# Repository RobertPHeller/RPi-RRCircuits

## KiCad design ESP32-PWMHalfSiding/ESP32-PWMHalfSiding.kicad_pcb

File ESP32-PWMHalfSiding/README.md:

# ESP32-PWMHalfSiding

This is a circuit board that supports an ESP32 Dev Kit board or TTGO-T1 board 
to manage one half (one end) of a siding.  This board can also be used to 
manage two bi-directional single track ABS blocks or one bi-directional dual 
track ABS block.  There are other trackwork cases this board can handle as 
well.  

The board contains these I/O sections:

- Two occupancy detectors.  These are optoisolator based, so they will 
  work for both DC and DCC systems.
- Two stall-motor with point sense.
- Sixteen PWM Led drivers.  These are meant to light lamps in signal 
  heads.

This board uses six GPIO pins and one I2C channel:

- **GPIO0** Motor Select 1: select the position of stall motor 1.
- **GPIO12** Motor Select 2: select the position of stall motor 2.
- **GPIO34** Point Sense 1: return the state of the points for 
  stall motor 1. 
- **GPIO35** Point Sense 2: return the state of the points for 
  stall motor 2. 
- **GPIO26** Occupancy Detector 1.
- **GPIO27** Occupancy Detector 2.
- **GPIO16** (Optional) Output enable for the PWM LED Controller.
- **I2C Address 0x40** A PCA9685 16-channel, 12-bit PWM LED Controller.

Each of the motor drive circuits is through a TC4428, which can drive up to
1.5A, which is way more needed to drive a typical stall motor. It is enough to
drive a pair of stall motors, wired in parallel as would be the case for a
cross over. 

## Circuit Description

[ESP32-PWMHalfSiding.pdf](https://github.com/RobertPHeller/RPi-RRCircuits/blob/master/ESP32-PWMHalfSiding/ESP32-PWMHalfSiding.pdf
)

### Turnout Control

The turnout control has two parts. There is an output section that contains
two TC4428 chips. Each chip has a non-inverting and an inverting driver. The
inputs of both drivers are connected to one of the motor GPIO pins. The output
are wired to the terminal block for a one of the motors. For any given logic
state of the motor control output, one of the drivers is ``on'' and the other
is ``off'', thus one motor terminal is ground and one is raised to the 12V
supply. This means alternative states of the logic line will drive the stall
motor in alternative directions. 

The other section is a pair of flip-flop debounce circuits, one for each of
two SPDT switch contacts that report the position of the turnout points. The
output of these flip-flops goes to a pair of GPIO input pins.

### CAN Transceiver

This section contains the CAN Transceiver, along with a termination jumper 
block. Power insertion and pick off and the RJ45 Jacks.

### Power Supply

This section contains a 5V power supply that takes the nominal 12V on the CAN 
power bus and regulates it down to 5V to supply the ESP32 MCU board.

### Occupancy Detectors

The occupancy detectors use optoisolators in series with the track power 
supply.  There is a heavy duty bridge rectifier in parallel with the 
optoisolators to carry the bulk of the current to the track.  They will work 
with either DC or DCC track power.

### PWM LED Driver

The PWM LED Driver uses a PCA9685 which is a 16 channel, 12 bit PWD LED 
driver.  A pair of octal MOSFET drivers and series load resistors are also 
included on the board.  The MOSFET drivers come in both inverting (low-side 
drive) and non-inverting (high-side drive), so it is possible to support both 
common anode and common cathode LED signals.  There are also (solder) jumpers 
on the board to support selecting the proper common wiring.

## Parts List

|Value|Qty|Refs|Mouser Part Number|
|-------|----|----------|------------------------------|  
|.1 uf|3|C1 C7 C601|21RZ310-RC|
|15 uf 15V|1|C2|710-860080773002|
|47 nf|1|C3|75-1C10Z5U473M050B|
|220 uf 25V|1|C4|140-REA221M1EBK0811P|
|22 uf 100V|1|C5|140-REA220M2ABK0811P|
|SB240E|3|D1 D2 D601|625-SB240-E3|
|SB160-E3/54|1|D3|625-SB160-E3|
|BRIDGEX|2|D4 D5|750-KBL401-G|
|MCT6H|2|IC1 IC2|782-MCT6H|
|RJ45|2|J1 J2|710-615008144221|
|Termination|1|JP1|649-67997-404HLF|
|330 uh|1|L1|673-PE-52627NL|
|Signal Terminals|2|P601 P602|651-1725724|
|60 Ohms|2|R1 R2|71-RN60C60R0B/R|
|10 Ohms|2|R3 R5|603-CFR-25JR-5210R|
|10K Ohms|2|R4 R6|603-CFR25SJT-52-10K|
|1.5K Ohms|2|RP601 RP602|652-4116R-1LF-1.5K|
|10K Ohms|1|RR2|652-4605X-AP1-103LF|
|Power Terminals|3|T1 T2 T601|651-1725656|
|Track Terminals|2|T3 T6|490-TB007-508-02BE|
|Turnout Terminals|2|T4 T5|651-1725685|
|ESP32_DEVKIT_C or TTGO-T1|1|U0|2x517-929974-01-19-RK (ESP32_DEVKIT_C) or 2x517-929850-01-18-10 (TTGO-T1)|
|TCAN332DR|1|U1|595-TCAN332DR|
|LM2574N-5.0|1|U3|926-LM2574N-5.0/NOPB|
|PCA9685|1|U601|771-PCA9685PW|
|TBD62X83A|2|U602 U603|757-TBD62083APG or 757-TBD62783APG|
|TC4428|2|U7 U8|579-TC4428VPA|
|74HCT00|1|U9|595-SN74AHC00N|

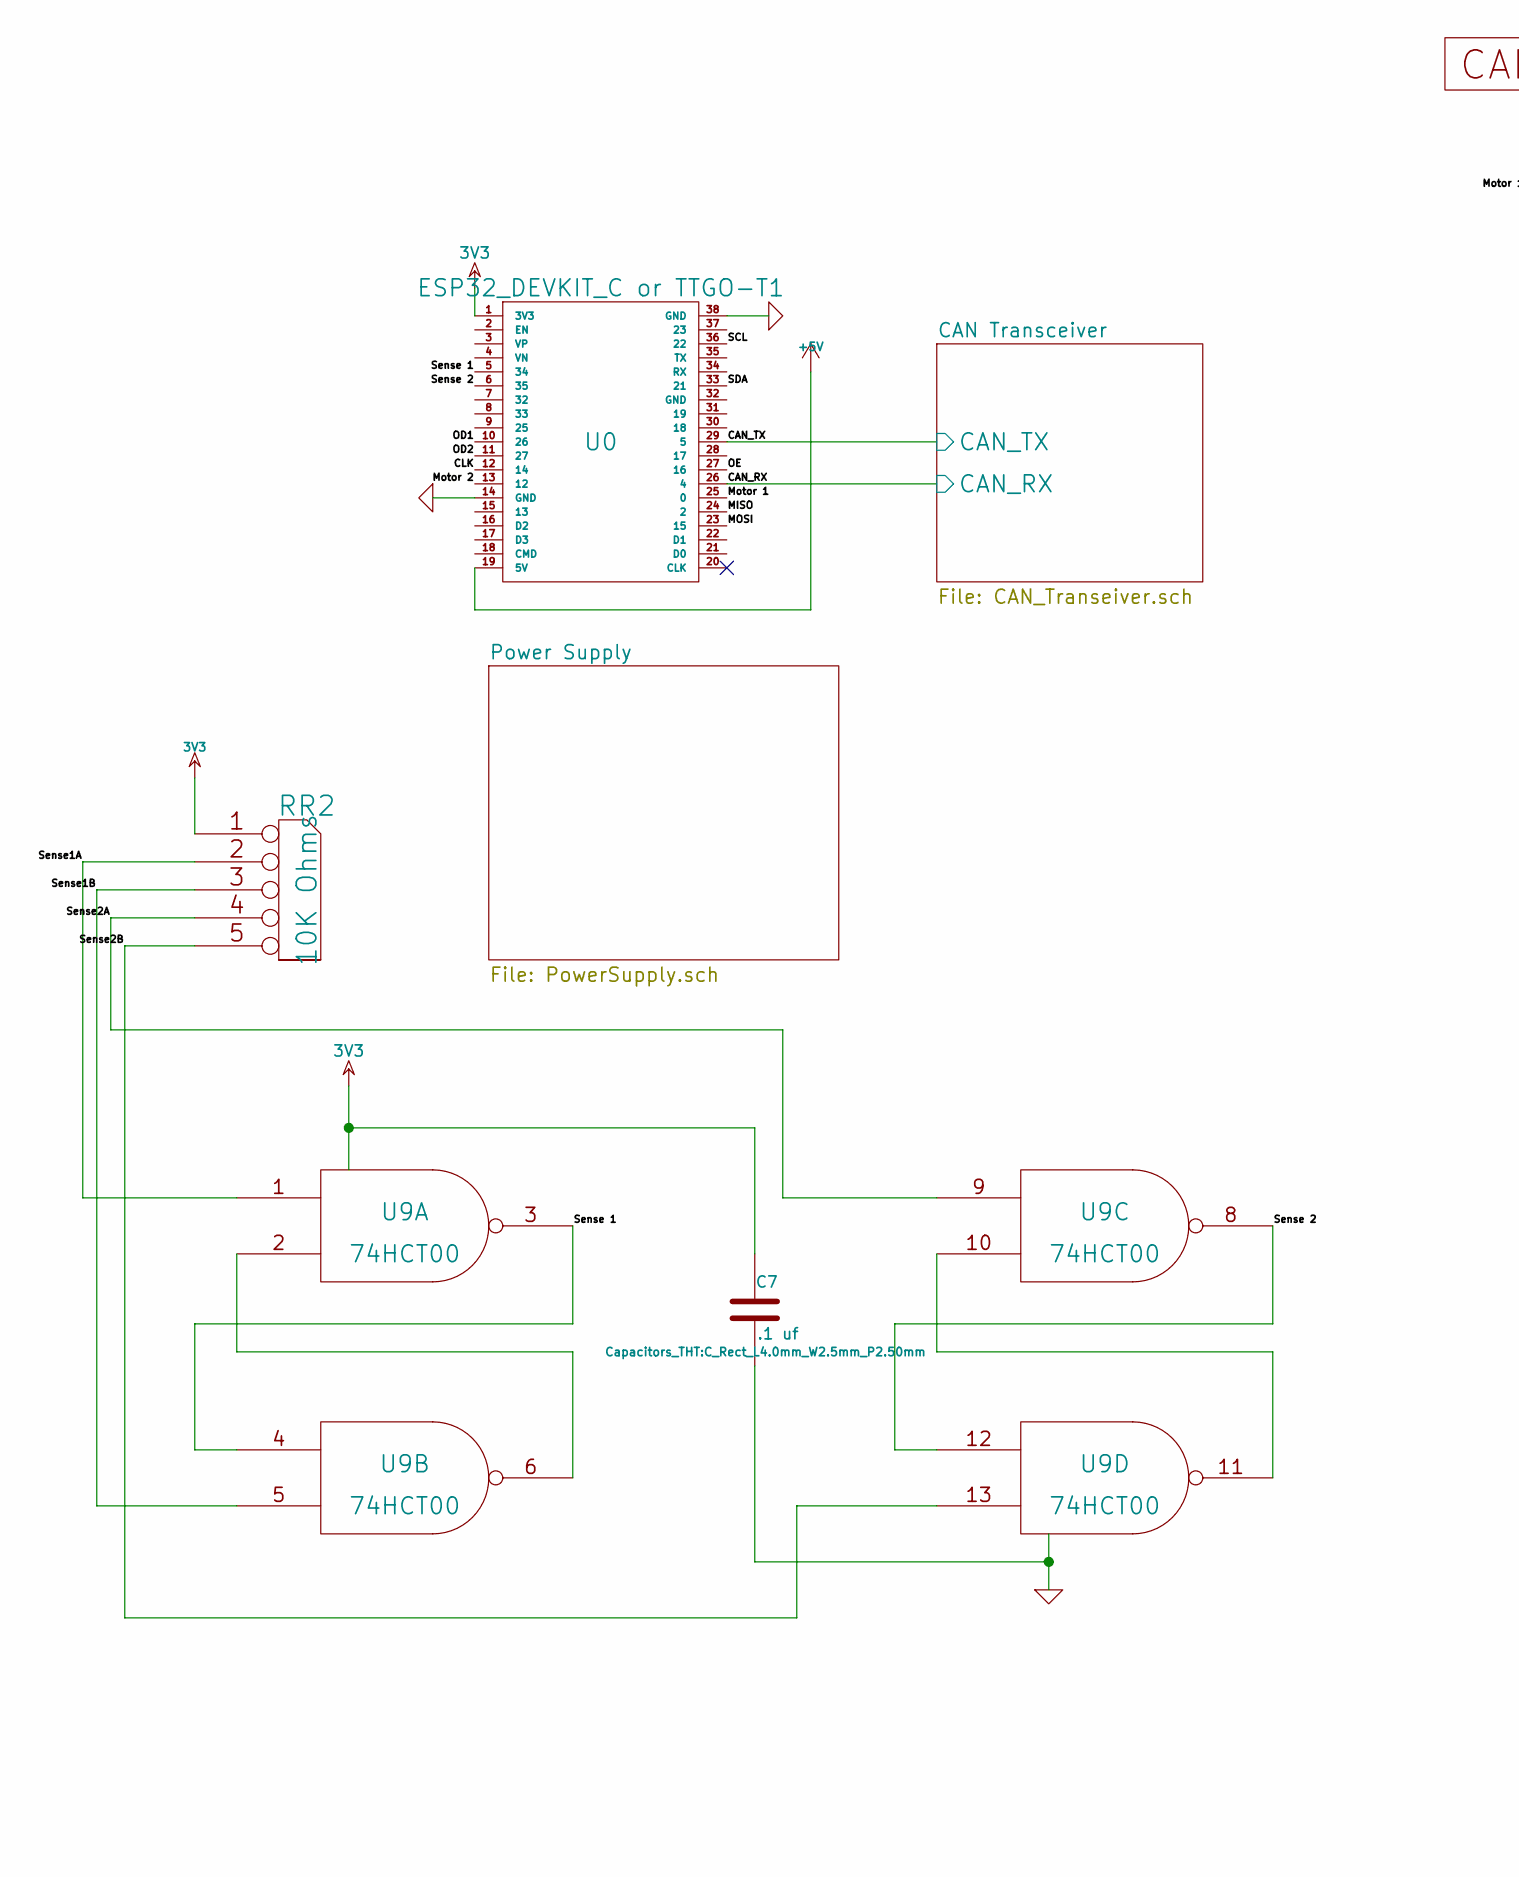
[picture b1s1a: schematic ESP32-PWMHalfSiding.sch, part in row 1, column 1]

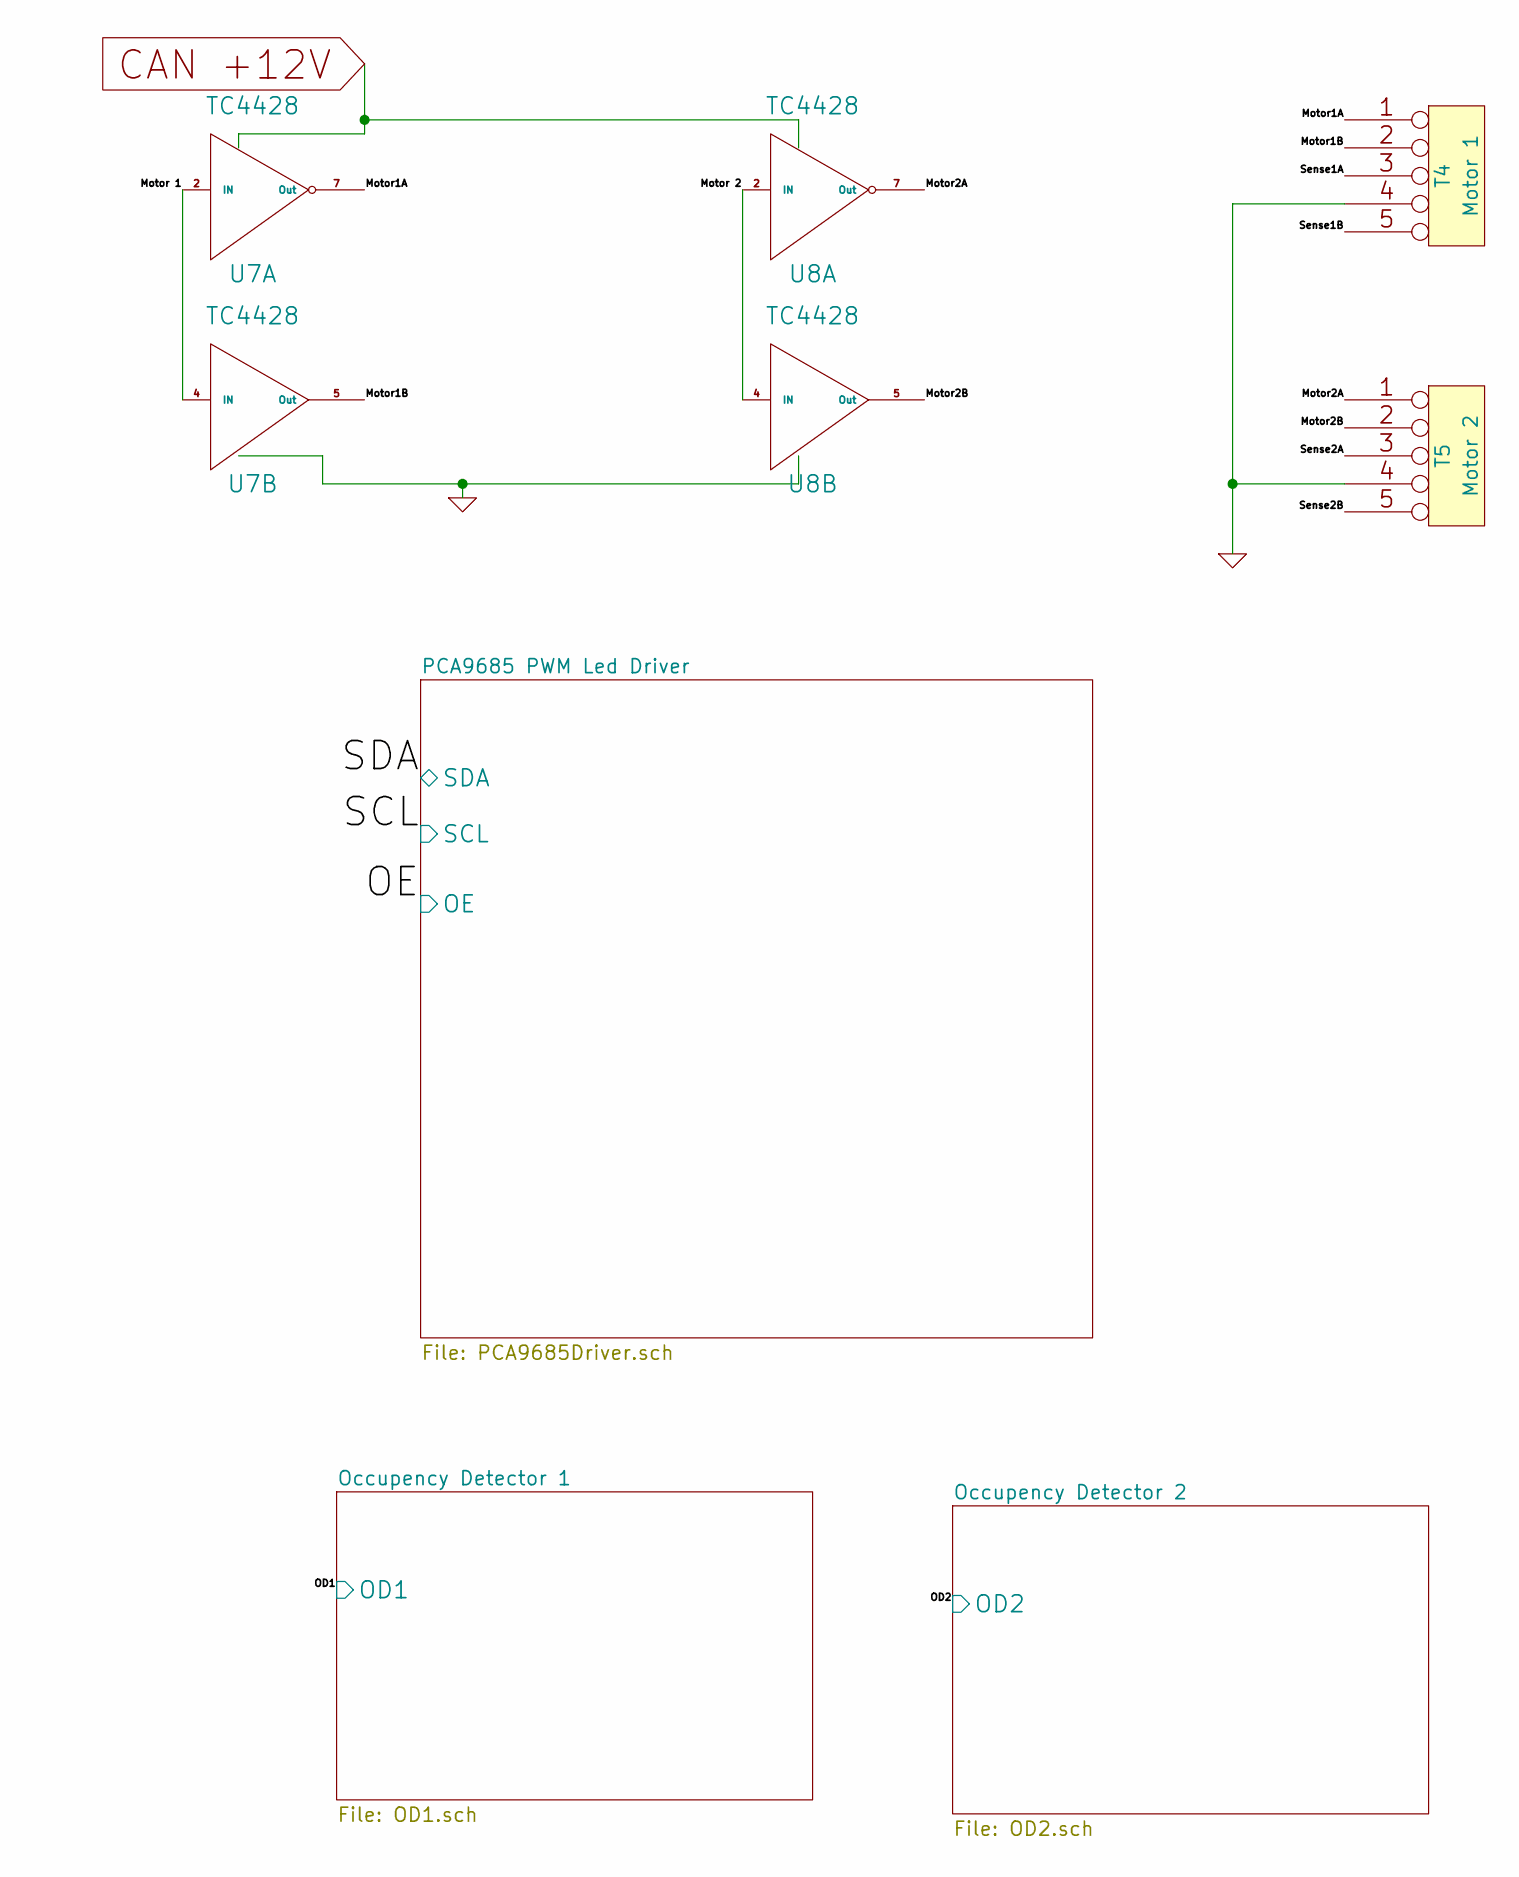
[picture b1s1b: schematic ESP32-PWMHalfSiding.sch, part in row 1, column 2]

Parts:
C7: .1 uf; C_Rect_L4.0mm_W2.5mm_P2.50mm; Mouser Part Number 21RZ310-RC
RR2: 10K Ohms; Mouser Part Number 652-4605X-AP1-103LF
T4: Motor 1; Mouser Part Number 651-1725685
T5: Motor 2; Mouser Part Number 651-1725685
U0: ESP32_DEVKIT_C or TTGO-T1
U7, U8: TC4428; Mouser Part Number 579-TC4428VPA
U9: 74HCT00; Mouser Part Number 595-SN74AHC00N

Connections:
3V3: C7.1, RR2.1 (COM), U0.1 (3V3), U9.14 (VCC); also elsewhere on the board
+5V: U0.19 (5V); also elsewhere on the board
/CAN_RX: U0.26 (4); also elsewhere on the board
/CAN_TX: U0.29 (5); also elsewhere on the board
/CLK: U0.12 (14); also elsewhere on the board
/MISO: U0.24 (2)
/MOSI: U0.23 (15)
/Motor1A: T4.1, U7.7 (Out)
/Motor1B: T4.2, U7.5 (Out)
/Motor2A: T5.1, U8.7 (Out)
/Motor2B: T5.2, U8.5 (Out)
/Motor 1: U0.25 (0), U7.2 (IN), U7.4 (IN); also elsewhere on the board
/Motor 2: U0.13 (12), U8.2 (IN), U8.4 (IN); also elsewhere on the board
/OD1: U0.10 (26); also elsewhere on the board
/OD2: U0.11 (27); also elsewhere on the board
/OE: U0.27 (16); also elsewhere on the board
/SCL: U0.36 (22); also elsewhere on the board
/SDA: U0.33 (21); also elsewhere on the board
/Sense1A: RR2.2, T4.3, U9.1
/Sense1B: RR2.3, T4.5, U9.5
/Sense2A: RR2.4, T5.3, U9.9
/Sense2B: RR2.5, T5.5, U9.13
/Sense 1: U0.5 (34), U9.3, U9.4; also elsewhere on the board
/Sense 2: U0.6 (35), U9.8, U9.12; also elsewhere on the board
CAN +12V: U7.6 (Vdd), U8.6 (Vdd); also elsewhere on the board
GND: C7.2, T4.4, T5.4, U0.14 (GND), U0.38 (GND), U7.3 (GND), U8.3 (GND), U9.7 (GND); also elsewhere on the board
unnamed 86: U0.2 (EN); also elsewhere on the board
unnamed 87: U0.3 (VP); also elsewhere on the board
unnamed 88: U0.4 (VN); also elsewhere on the board
unnamed 89: U0.7 (32); also elsewhere on the board
unnamed 90: U0.8 (33); also elsewhere on the board
unnamed 91: U0.9 (25); also elsewhere on the board
unnamed 92: U0.15 (13); also elsewhere on the board
unnamed 93: U0.16 (D2); also elsewhere on the board
unnamed 94: U0.17 (D3); also elsewhere on the board
unnamed 95: U0.18 (CMD); also elsewhere on the board
unnamed: U9.2, U9.6
unnamed: U9.10, U9.11

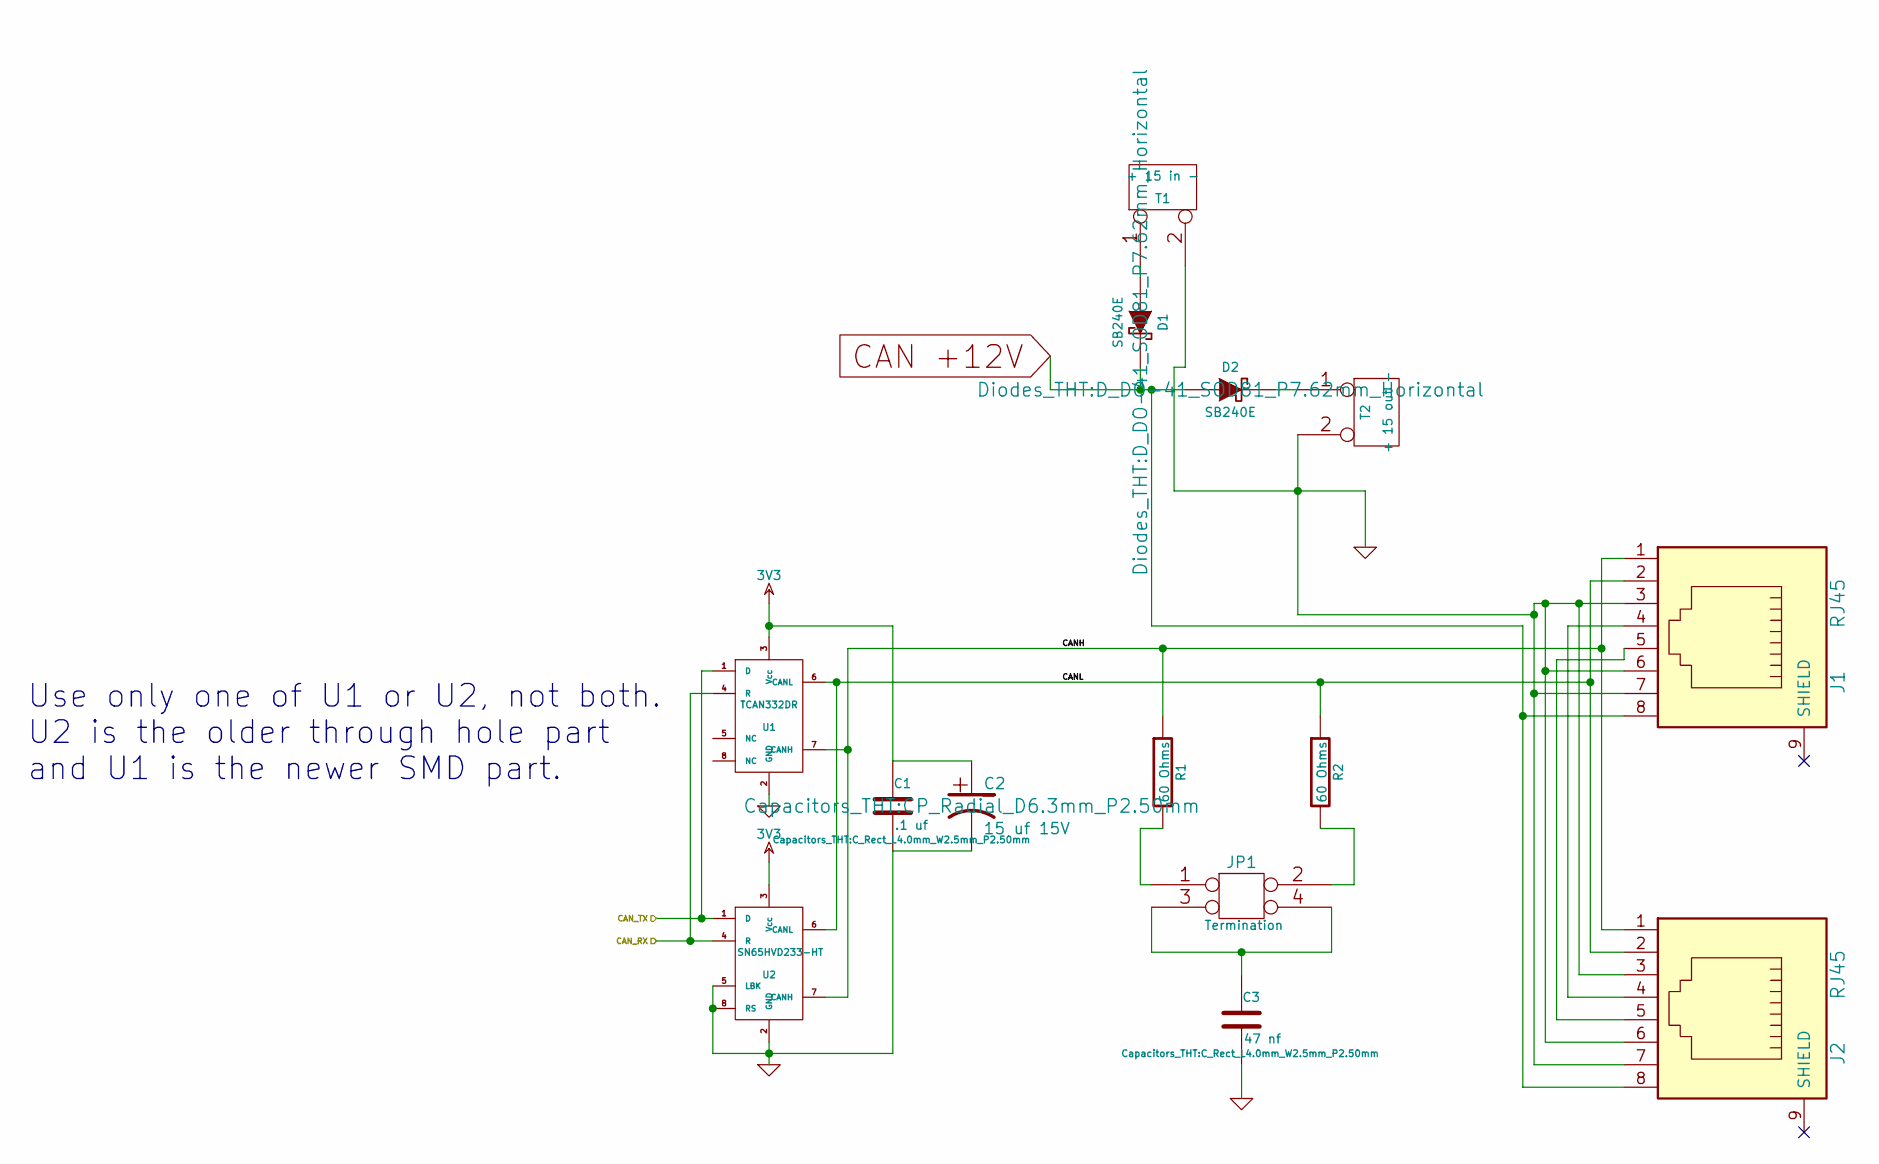
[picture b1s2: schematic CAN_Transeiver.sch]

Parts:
C1: .1 uf; C_Rect_L4.0mm_W2.5mm_P2.50mm; Mouser Part Number 21RZ310-RC
C2: 15 uf 15V; CP_Radial_D6.3mm_P2.50mm; Mouser Part Number 710-860080773002
C3: 47 nf; C_Rect_L4.0mm_W2.5mm_P2.50mm; Mouser Part Number 75-1C10Z5U473M050B
D1, D2: SB240E; D_DO-41_SOD81_P7.62mm_Horizontal; Mouser Part Number 625-SB240-E3
J1, J2: RJ45; RJ45_8; Mouser Part Number 710-615008144221
JP1: Termination; Mouser Part Number 649-67997-404HLF
R1, R2: 60 Ohms; Mouser Part Number 71-RN60C60R0B/R
T1: + 15 in -; Mouser Part Number 651-1725656
T2: + 15 out -; Mouser Part Number 651-1725656
U1: TCAN332DR; Mouser Part Number 595-TCAN332DR
U2: SN65HVD233-HT

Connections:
3V3: C1.1, C2.1, U1.3 (Vcc), U2.3 (Vcc); also elsewhere on the board
/CAN Transceiver/CANH: J1.1, J2.1, R1.1, U1.7 (CANH), U2.7 (CANH)
/CAN Transceiver/CANL: J1.2, J2.2, R2.1, U1.6 (CANL), U2.6 (CANL)
/CAN_RX: U1.4 (R), U2.4 (R); also elsewhere on the board
/CAN_TX: U1.1 (D), U2.1 (D); also elsewhere on the board
CAN +12V: D1.2 (K), D2.1 (A), J1.8, J2.8; also elsewhere on the board
GND: C1.2, C2.2, C3.2, J1.3, J1.6, J1.7, J2.3, J2.6, J2.7, T1.2 (PM), T2.2 (PM), U1.2 (GND), U2.2 (GND), U2.5 (LBK), U2.8 (RS); also elsewhere on the board
unnamed: C3.1, JP1.3, JP1.4
unnamed: D1.1 (A), T1.1
unnamed: D2.2 (K), T2.1
unnamed: J1.4, J2.4
unnamed: J1.5, J2.5
unnamed: JP1.1, R1.2
unnamed: JP1.2, R2.2

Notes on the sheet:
Use only one of U1 or U2, not both. U2 is the older through hole part and U1 is the newer SMD part.

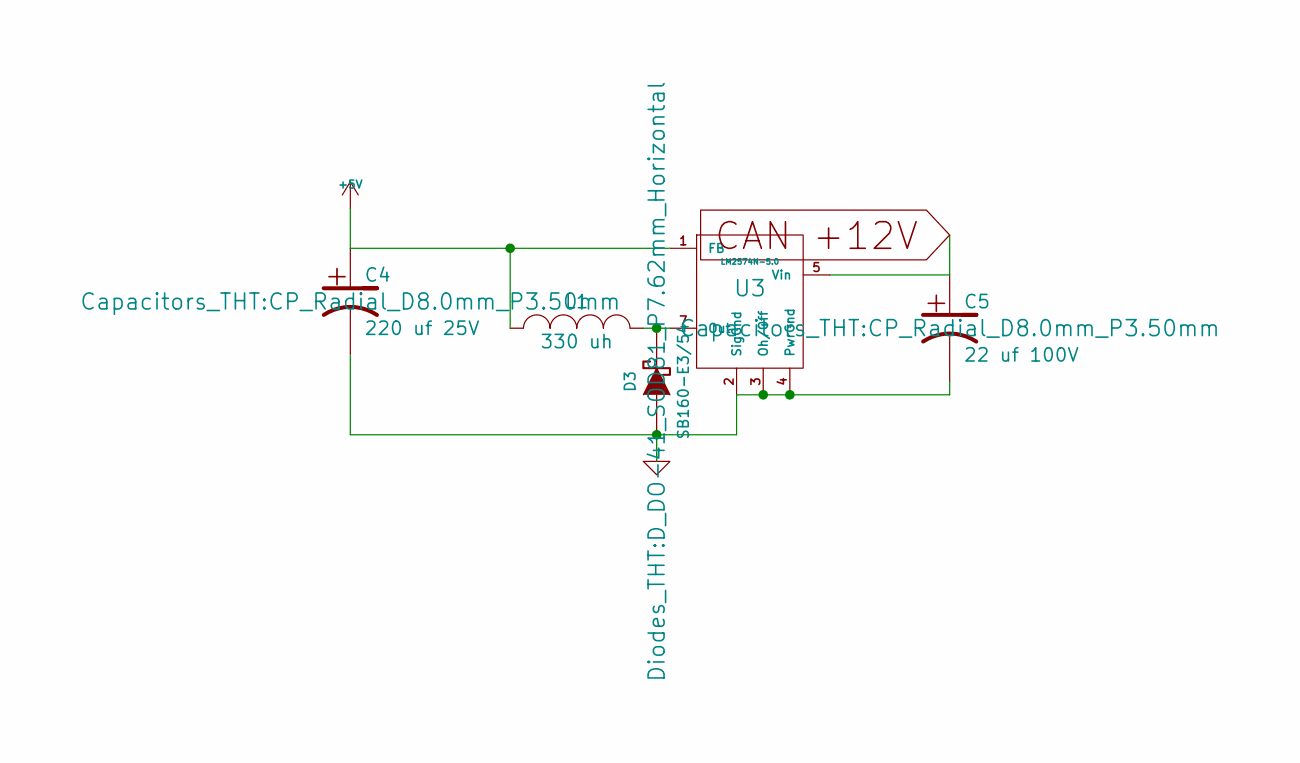
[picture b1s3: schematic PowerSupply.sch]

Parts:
C4: 220 uf 25V; CP_Radial_D8.0mm_P3.50mm; Mouser Part Number 140-REA221M1EBK0811P
C5: 22 uf 100V; CP_Radial_D8.0mm_P3.50mm; Mouser Part Number 140-REA220M2ABK0811P
D3: SB160-E3/54; D_DO-41_SOD81_P7.62mm_Horizontal; Mouser Part Number 625-SB160-E3
L1: 330 uh; Mouser Part Number 673-PE-52627NL
U3: LM2574N-5.0; Mouser Part Number 926-LM2574N-5.0/NOPB

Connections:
+5V: C4.1, L1.1, U3.1 (FB); also elsewhere on the board
CAN +12V: C5.1, U3.5 (Vin); also elsewhere on the board
GND: C4.2, C5.2, D3.1 (A), U3.2 (SigGnd), U3.3 (Oh/Off), U3.4 (PwrGnd); also elsewhere on the board
unnamed: D3.2 (K), L1.2, U3.7 (Out)

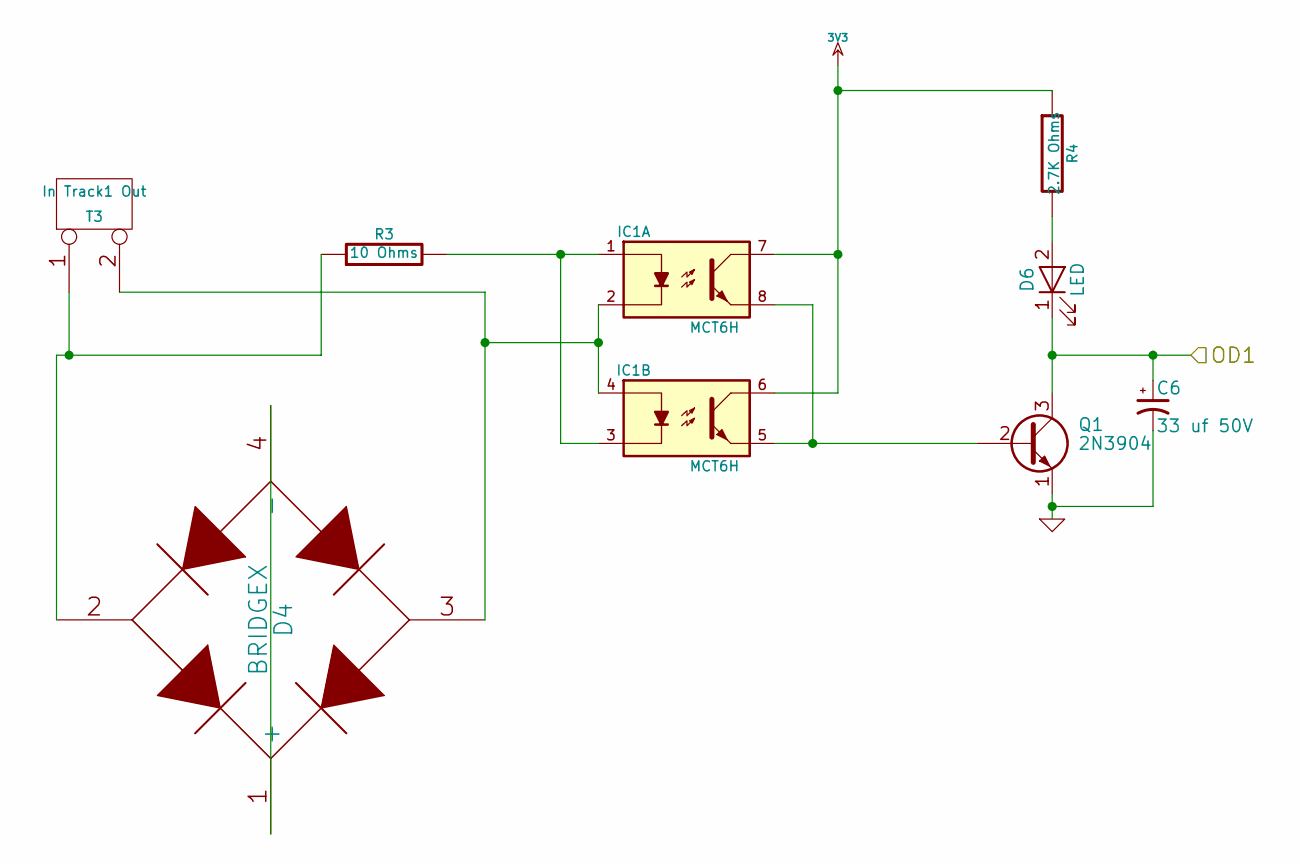
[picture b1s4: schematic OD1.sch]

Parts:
C6: 33 uf 50V; CP_Radial_D6.3mm_P2.50mm
D4: BRIDGEX; Mouser Part Number 750-KBL401-G
D6: LED; LED_D3.0mm
IC1: MCT6H; DIP-8_W7.62mm; Mouser Part Number 782-MCT6H
Q1: 2N3904; TO-92_Molded_Narrow
R3: 10 Ohms; Mouser Part Number 603-CFR-25JR-5210R
R4: 2.7K Ohms; Mouser Part Number 603-CFR25SJT-52-10K
T3: In Track1 Out; Mouser Part Number 490-TB007-508-02BE

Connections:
3V3: IC1.6, IC1.7, R4.1; also elsewhere on the board
/OD1: C6.1, D6.1 (K), Q1.3 (C); also elsewhere on the board
GND: C6.2, Q1.1 (E); also elsewhere on the board
unnamed: D4.1 (+), D4.4 (-)
unnamed: D4.2, R3.1, T3.1
unnamed: D4.3, IC1.2, IC1.4, T3.2 (PM)
unnamed: D6.2 (A), R4.2
unnamed: IC1.1, IC1.3, R3.2
unnamed: IC1.5, IC1.8, Q1.2 (B)

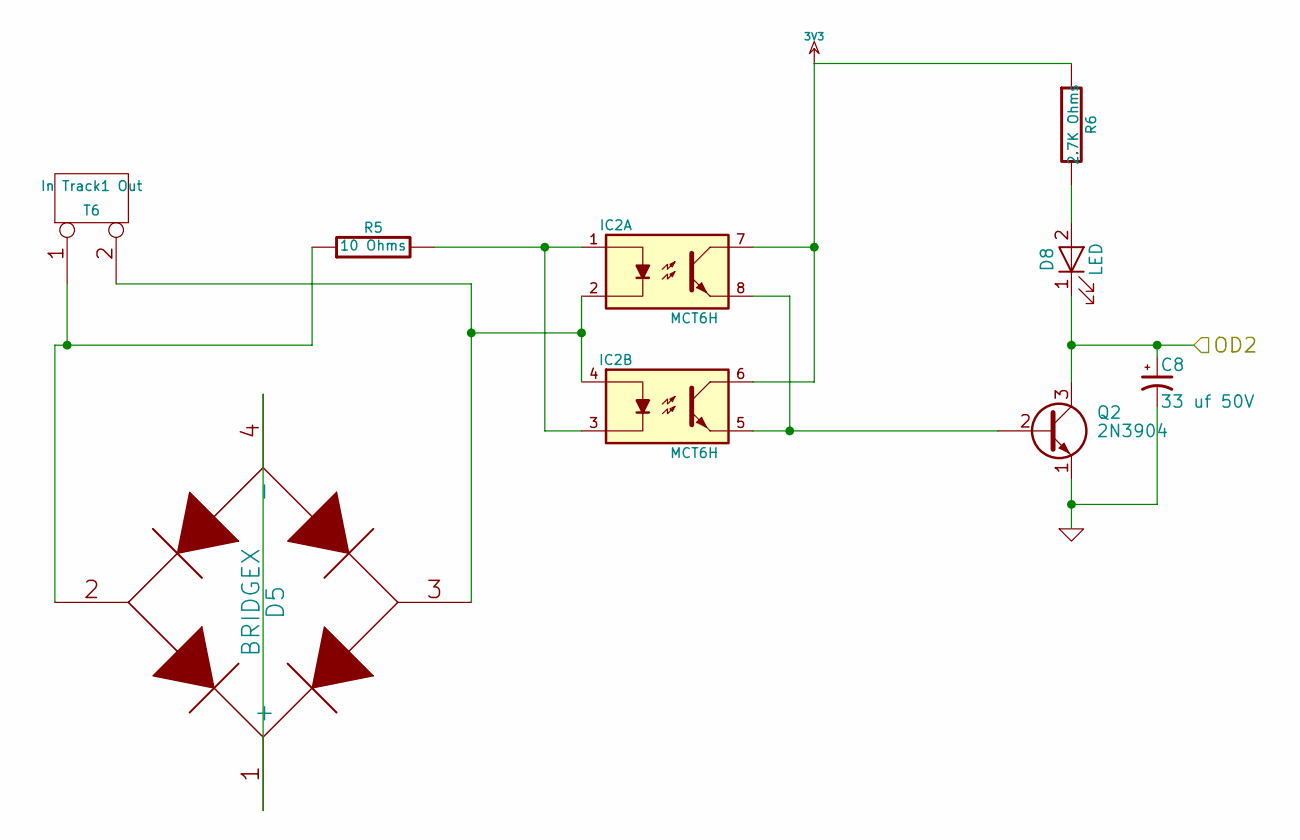
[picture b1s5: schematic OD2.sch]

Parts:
C8: 33 uf 50V; CP_Radial_D6.3mm_P2.50mm
D5: BRIDGEX; Mouser Part Number 750-KBL401-G
D8: LED; LED_D3.0mm
IC2: MCT6H; DIP-8_W7.62mm; Mouser Part Number 782-MCT6H
Q2: 2N3904; TO-92_Molded_Narrow
R5: 10 Ohms; Mouser Part Number 603-CFR-25JR-5210R
R6: 2.7K Ohms; Mouser Part Number 603-CFR25SJT-52-10K
T6: In Track1 Out; Mouser Part Number 490-TB007-508-02BE

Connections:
3V3: IC2.6, IC2.7, R6.1; also elsewhere on the board
/OD2: C8.1, D8.1 (K), Q2.3 (C); also elsewhere on the board
GND: C8.2, Q2.1 (E); also elsewhere on the board
unnamed: D5.1 (+), D5.4 (-)
unnamed: D5.2, R5.1, T6.1
unnamed: D5.3, IC2.2, IC2.4, T6.2 (PM)
unnamed: D8.2 (A), R6.2
unnamed: IC2.1, IC2.3, R5.2
unnamed: IC2.5, IC2.8, Q2.2 (B)

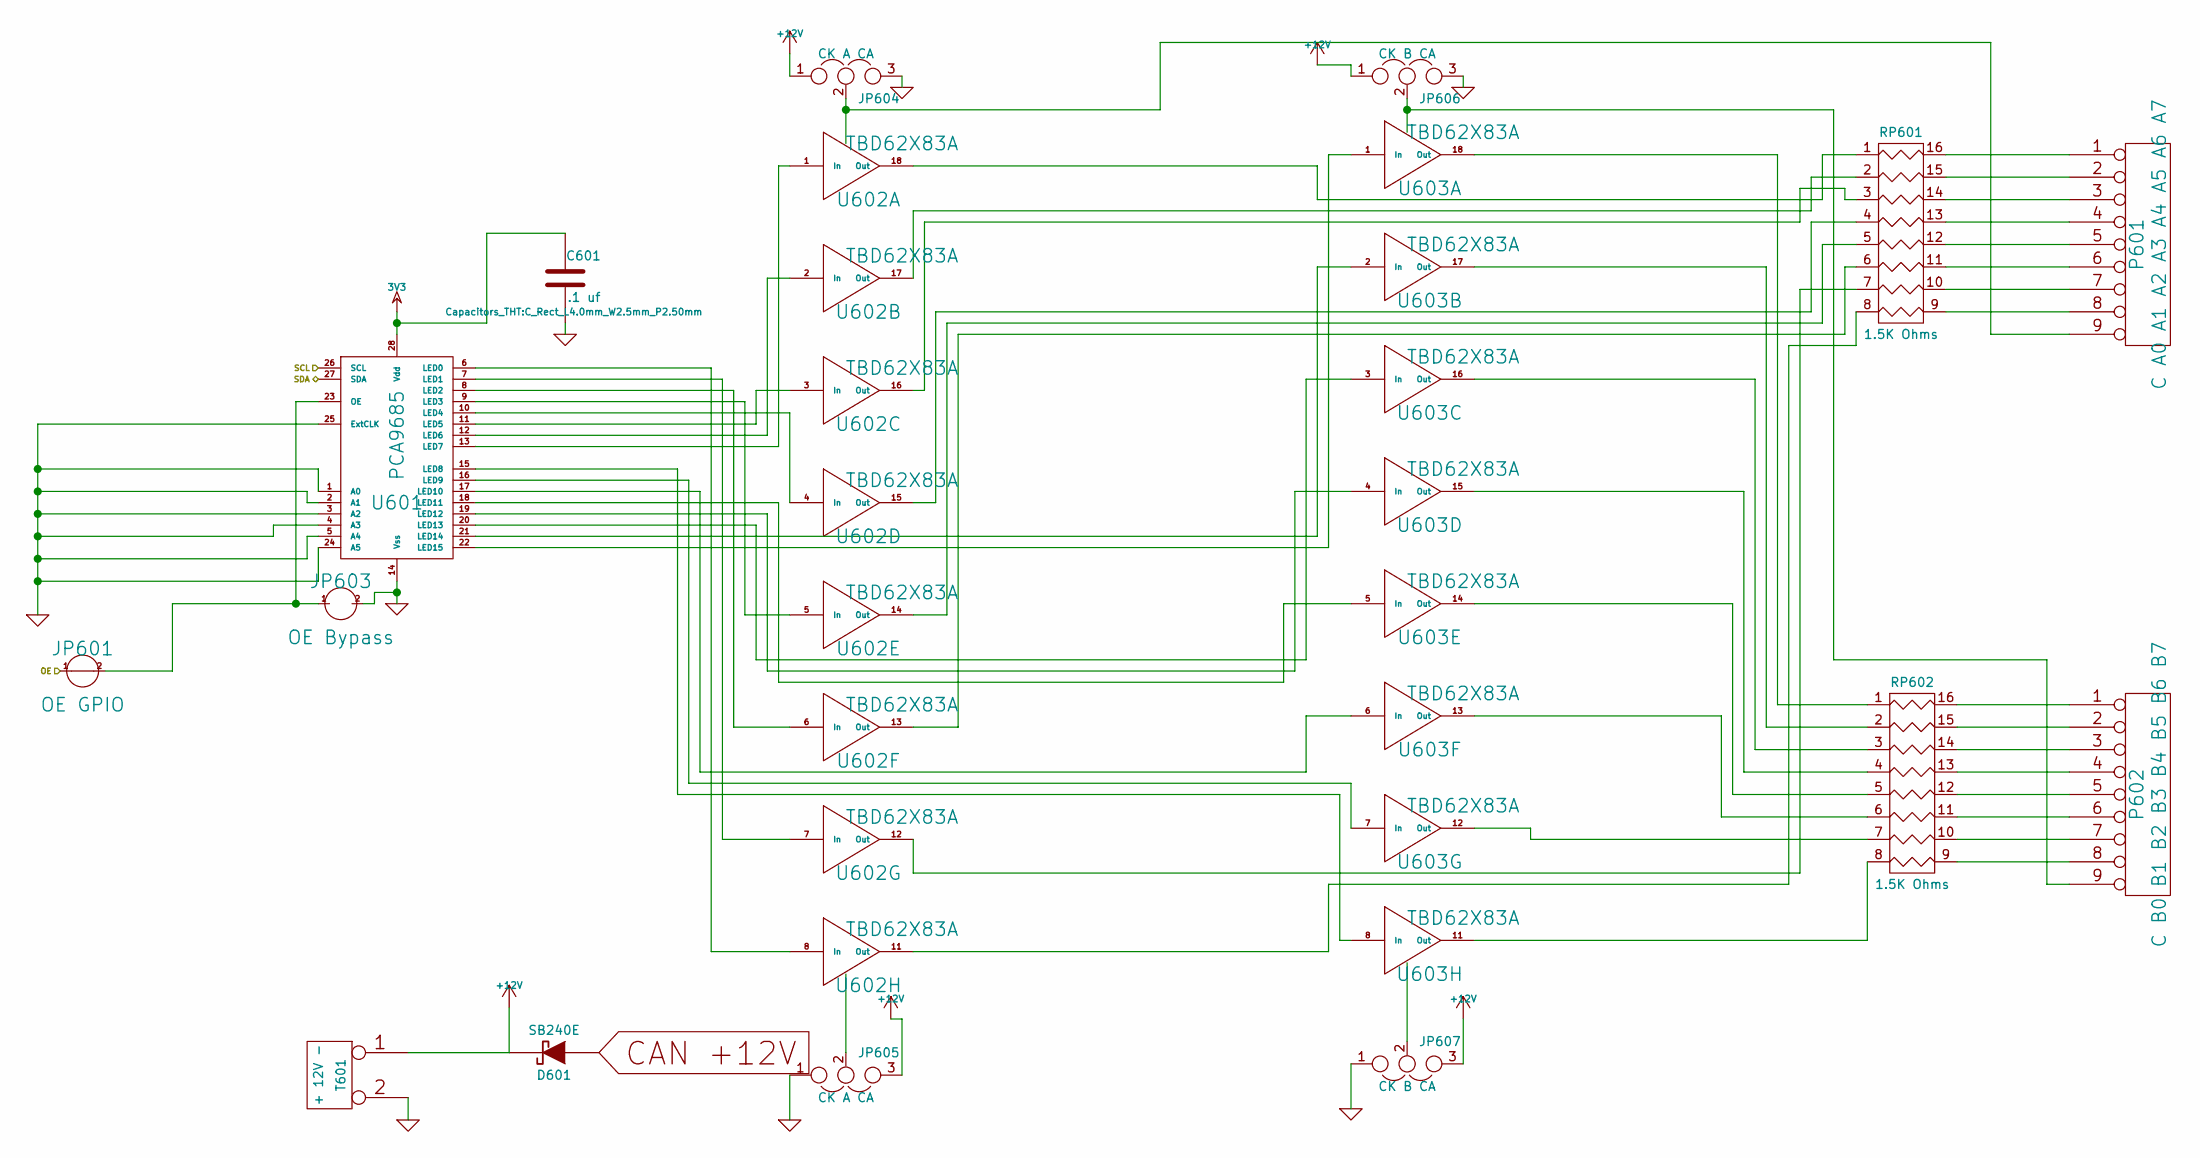
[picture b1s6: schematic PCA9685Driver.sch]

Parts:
C601: .1 uf; C_Rect_L4.0mm_W2.5mm_P2.50mm; Mouser Part Number 21RZ310-RC
D601: SB240E; D_DO-41_SOD81_P7.62mm_Horizontal; Mouser Part Number 625-SB240-E3
JP601: OE GPIO
JP603: OE Bypass
JP604, JP605: CK A CA
JP606, JP607: CK B CA
P601: C A0 A1 A2 A3 A4 A5 A6 A7; Mouser Part Number 651-1725724
P602: C B0 B1 B2 B3 B4 B5 B6 B7; Mouser Part Number 651-1725724
RP601, RP602: 1.5K Ohms; Mouser Part Number 652-4116R-1LF-1.5K
T601: + 12V -; Mouser Part Number 651-1725656
U601: PCA9685; Mouser Part Number 771-PCA9685PW,118
U602, U603: TBD62X83A; Mouser Part Number 757-TBD62083APG or 757-TBD62783APG

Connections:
3V3: C601.1, U601.28 (Vdd); also elsewhere on the board
+12V: D601.2 (K), JP604.1, JP605.3, JP606.1, JP607.3, T601.1
/OE: JP601.1; also elsewhere on the board
/SCL: U601.26 (SCL); also elsewhere on the board
/SDA: U601.27 (SDA); also elsewhere on the board
CAN +12V: D601.1 (A); also elsewhere on the board
GND: C601.2, JP603.2, JP604.3, JP605.1, JP606.3, JP607.1, T601.2 (PM), U601.1 (A0), U601.2 (A1), U601.3 (A2), U601.4 (A3), U601.5 (A4), U601.14 (Vss), U601.24 (A5), U601.25 (ExtCLK); also elsewhere on the board
unnamed: JP601.2, JP603.1, U601.23 (OE)
unnamed: JP604.2, P601.9, U602.10 (OC)
unnamed: JP605.2, U602.9 (IC)
unnamed: JP606.2, P602.9, U603.10 (OC)
unnamed: JP607.2, U603.9 (IC)
unnamed: P601.1, RP601.16 (R1)
unnamed: P601.2, RP601.15 (R2)
unnamed: P601.3, RP601.14 (R3)
unnamed: P601.4, RP601.13 (R4)
unnamed: P601.5, RP601.12 (R5)
unnamed: P601.6, RP601.11 (R6)
unnamed: P601.7, RP601.10 (R7)
unnamed: P601.8, RP601.9 (R8)
unnamed: P602.1, RP602.16 (R1)
unnamed: P602.2, RP602.15 (R2)
unnamed: P602.3, RP602.14 (R3)
unnamed: P602.4, RP602.13 (R4)
unnamed: P602.5, RP602.12 (R5)
unnamed: P602.6, RP602.11 (R6)
unnamed: P602.7, RP602.10 (R7)
unnamed: P602.8, RP602.9 (R8)
unnamed: RP601.1, U602.18 (Out)
unnamed: RP601.2, U602.17 (Out)
unnamed: RP601.3, U602.16 (Out)
unnamed: RP601.4, U602.15 (Out)
unnamed: RP601.5, U602.14 (Out)
unnamed: RP601.6, U602.13 (Out)
unnamed: RP601.7, U602.12 (Out)
unnamed: RP601.8, U602.11 (Out)
unnamed: RP602.1, U603.18 (Out)
unnamed: RP602.2, U603.17 (Out)
unnamed: RP602.3, U603.16 (Out)
unnamed: RP602.4, U603.15 (Out)
unnamed: RP602.5, U603.14 (Out)
unnamed: RP602.6, U603.13 (Out)
unnamed: RP602.7, U603.12 (Out)
unnamed: RP602.8, U603.11 (Out)
unnamed: U601.6 (LED0), U602.8 (In)
unnamed: U601.7 (LED1), U602.7 (In)
unnamed: U601.8 (LED2), U602.6 (In)
unnamed: U601.9 (LED3), U602.5 (In)
unnamed: U601.10 (LED4), U602.4 (In)
unnamed: U601.11 (LED5), U602.3 (In)
unnamed: U601.12 (LED6), U602.2 (In)
unnamed: U601.13 (LED7), U602.1 (In)
unnamed: U601.15 (LED8), U603.8 (In)
unnamed: U601.16 (LED9), U603.7 (In)
unnamed: U601.17 (LED10), U603.6 (In)
unnamed: U601.18 (LED11), U603.5 (In)
unnamed: U601.19 (LED12), U603.4 (In)
unnamed: U601.20 (LED13), U603.3 (In)
unnamed: U601.21 (LED14), U603.2 (In)
unnamed: U601.22 (LED15), U603.1 (In)

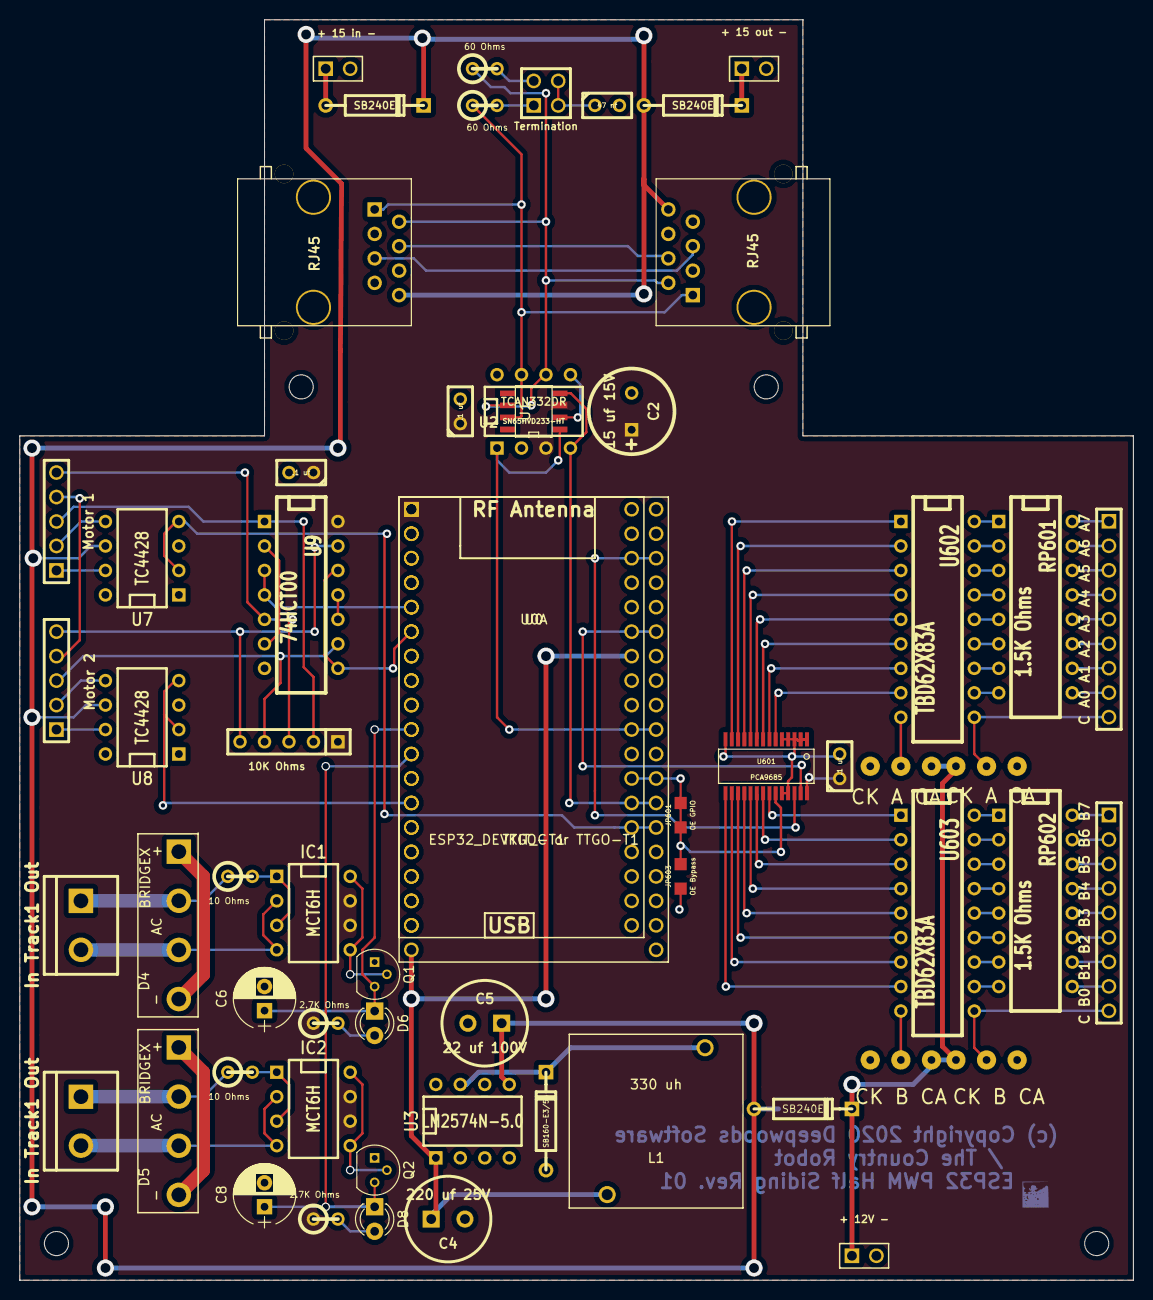
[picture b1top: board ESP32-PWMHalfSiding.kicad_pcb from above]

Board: 2 copper layers, 115.6 x 130.8 mm, 64 parts (0 on the bottom side), 112 nets.

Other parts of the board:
MH: MountingHole_2-5mm_RevA_Date21Jun2010
MH#2, MH#3, MH#4: MountingHole_2-5mm_RevA_Date21Jun2010
U0A: TTGO-T1; TIGO-T1

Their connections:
3V3: U0A.1; also elsewhere on the board
+5V: U0A.30; also elsewhere on the board
/CAN_RX: U0A.24; also elsewhere on the board
/CAN_TX: U0A.27; also elsewhere on the board
/CLK: U0A.12; also elsewhere on the board
/Motor 1: U0A.23; also elsewhere on the board
/Motor 2: U0A.13; also elsewhere on the board
/OD1: U0A.10; also elsewhere on the board
/OD2: U0A.11; also elsewhere on the board
/OE: U0A.25; also elsewhere on the board
/SCL: U0A.34; also elsewhere on the board
/SDA: U0A.31; also elsewhere on the board
/Sense 1: U0A.5; also elsewhere on the board
/Sense 2: U0A.6; also elsewhere on the board
GND: U0A.14, U0A.36; also elsewhere on the board
unnamed 86: U0A.2; also elsewhere on the board
unnamed 87: U0A.3; also elsewhere on the board
unnamed 88: U0A.4; also elsewhere on the board
unnamed 89: U0A.7; also elsewhere on the board
unnamed 90: U0A.8; also elsewhere on the board
unnamed 91: U0A.9; also elsewhere on the board
unnamed 92: U0A.15; also elsewhere on the board
unnamed 93: U0A.16; also elsewhere on the board
unnamed 94: U0A.17; also elsewhere on the board
unnamed 95: U0A.18; also elsewhere on the board

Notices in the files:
ESP32-PWMHalfSiding/ESP32-PWMHalfSiding.kicad_pcb:
(c) Copyright 2020 Deepwoods Software
